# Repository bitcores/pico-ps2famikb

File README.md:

# pico-usb2famikb
Raspberry Pi Pico driven multi device emulator and Keyboard and Mouse Host for Famicom/NES by direct USB input or with an i2c host device

Emulates
* Family Basic Keyboard
* Subor Keyboard and Mouse
* Hori Track

And supports Keyboard and Mouse Host mode, a community developed serialized keyboard and mouse interface.

- \* D0 is only needed for subor mouse support. Connecting it will conflict with controller 2, it can be left disconnected. 4016 D1 shares this pin, it is only needed for Hori Track support on Famicom.
- \# D1 and D2 are only needed for Family Basic Keyboard mode, these can be left disconnected (esp. if making for NES player 2 controller port)
- \? USB D+ and D- lines are only needed for direct input. These can be left disconnected if only the i2c Host will be used (i2c Host EN can then be tied to 3.3V to permanently enable it)

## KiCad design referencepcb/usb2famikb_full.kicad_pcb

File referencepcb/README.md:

# pico-usb2famikb Reference PCBs
This directory contains reference PCB designs for the pico-usb2famikb. They have not been designed by a experienced engineer, but they DO work.

If you have some experience designing circuits like this, I would very much welcome improved designs.

For the full featured reference design you will need:
* 1x Raspberry Pi Pico
* 1x diode (I am using a 1N5819)
* 1x push button
* 1x 15pin d-sub VGA connector (for expansion port)
* 1x USB A type female port
* 2x 22ohm resistors
* 1x 100uf 16v capacitor (input from console)
* 1x 330uf 16v capacitor
* 2x four-channel logic level converters
* 13x pin headers (and some jumpers)

Note: The 330uf capactior was added because some USB3 hubs seem to draw significant power on startup can could crash the console or Pico, or both. The USB2 hubs I tested don't seem affected, but you can also just plug everything in before you turn on the console to avoid any issues.

## Wiring guide
The expansion port connector is laid out as follows when viewed from the top.

It is wired following the pinout of the [Famicom Expansion Port](https://www.nesdev.org/wiki/Expansion_port), 01 to 01, 15 to 15.
Wiring for the NES is more complicated, please reference both the tables on that page for wiring.

## Jumper guide
### KB Mode
The pico-usb2famikb can operate in four different modes:
 - Keyboard Mouse Host
 - Family Basic Keyboard
 - Subor Keyboard and Mouse
 - Family Basic Keyboard and HoriTrack

These modes are selected by setting the KBMode jumpers before power on (or reset).

 - No jumpers = Keyboard Mouse Host
 - One jumper on KBMode 1 = Family Basic Keyboard
 - One jumper on KBMode 2 = Subor Keyboard and Mouse
 - Two jumpers on KBMode 1 and 2 = Family Basic Keyboard and HoriTrack

### 4016D1/4017D0
HoriTrack and Subor Mouse require an extra data line which may interfere with controllers if left permanantly connected.

 - 4017d0 for Subor Mouse
 - 4016d1 for HoriTrack

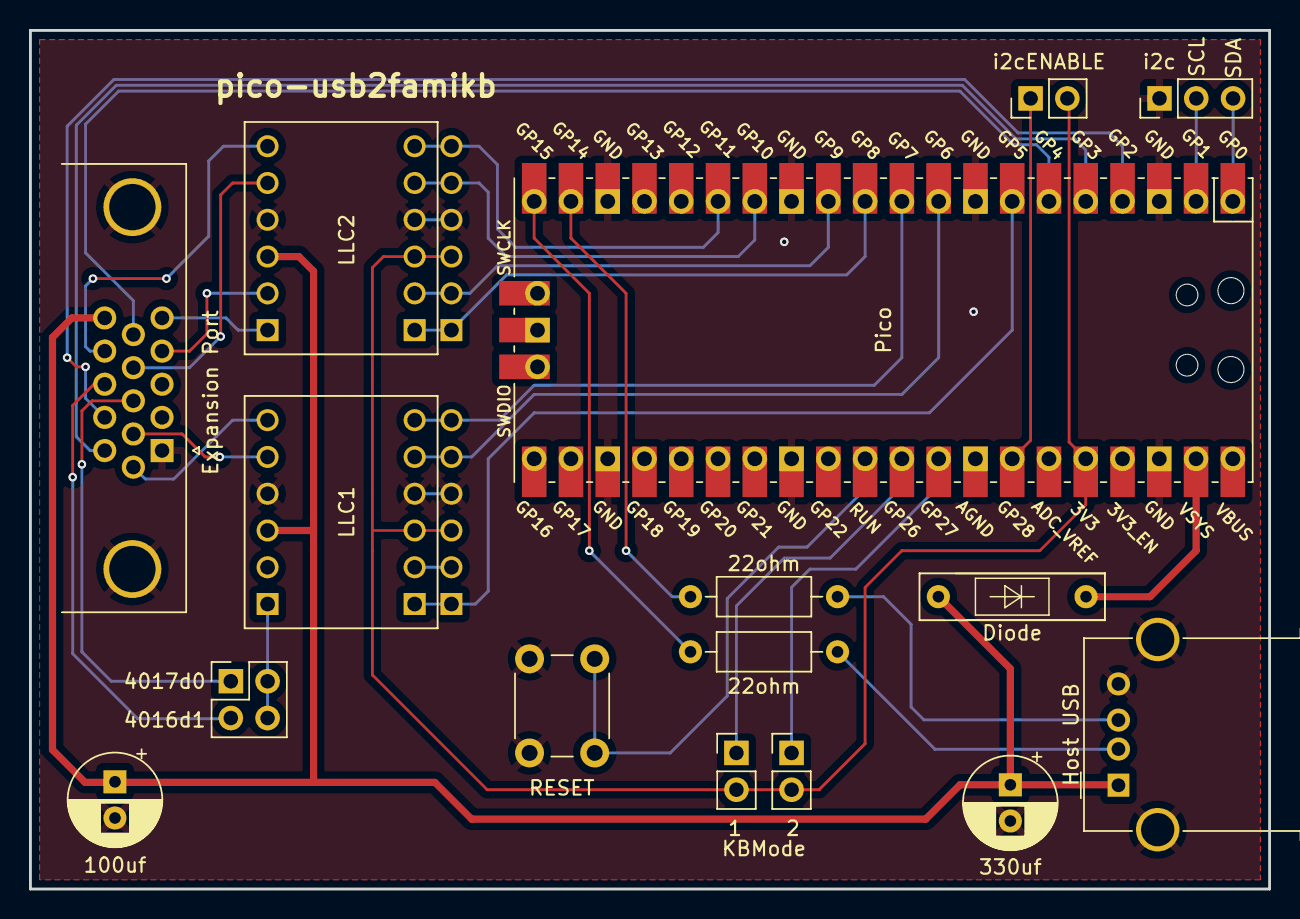
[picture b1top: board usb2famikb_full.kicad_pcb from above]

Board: 2 copper layers, 85.6 x 59.3 mm, 16 parts (0 on the bottom side), 33 nets.

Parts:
1    2: PinHeader_1x02_P2.54mm_Vertical
22ohm, 22ohm#2: R_Axial_DIN0207_L6.3mm_D2.5mm_P10.16mm_Horizontal
100uf, 330uf: CP_Radial_D6.3mm_P2.50mm
4017d0: PinHeader_2x02_P2.54mm_Vertical
Diode: D_MELF-RM10_Universal_Handsoldering
Expansion Port: DSUB-15-HD_Female_Horizontal_P2.29x1.98mm_EdgePin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; DSUB-15-HD_Female_Horizontal_P2.29x1.98mm_EdgePinOffset3.03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
Host USB: USB_A_Molex_67643_Horizontal
KBMode: PinHeader_1x02_P2.54mm_Vertical
LLC1, LLC2: CONV_BOB-12009
Pico: RPi_Pico_SMD_TH
RESET: SW_PUSH_6mm
i2c: PinHeader_1x03_P2.54mm_Vertical
i2cENABLE: PinHeader_1x02_P2.54mm_Vertical

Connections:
4016d1: 4017d0.3, Expansion Port.13
4016oe: Expansion Port.14, LLC2.HV4
4017d0: 4017d0.1, Expansion Port.8
4017d1: Expansion Port.7, LLC1.HV3
4017d2: Expansion Port.6, LLC1.HV4
4017d3: Expansion Port.5, LLC2.HV1
4017d4: Expansion Port.4, LLC2.HV2
4017oe: Expansion Port.9, LLC2.HV3
+3.3v: 1 2.2, KBMode.2, LLC1.LV, LLC2.LV, Pico.36, i2cENABLE.2
+5v: 100uf.1, 330uf.1, Diode.2, Expansion Port.15, Host USB.1, LLC1.HV, LLC2.HV
GND: 100uf.2, 330uf.2, Expansion Port.0, Expansion Port.1, Host USB.4, Host USB.5, LLC1.GND_1, LLC1.GND_2, LLC2.GND_1, LLC2.GND_2, Pico.3, Pico.8, Pico.13, Pico.18, Pico.23, Pico.28, Pico.33, Pico.38, RESET.2, i2c.1
fcd0d1: 4017d0.2, 4017d0.4, LLC1.HV1
fcout0: Expansion Port.12, Pico.4
fcout1: Expansion Port.11, Pico.5
fcout2: Expansion Port.10, Pico.6
i2c1: Pico.1, i2c.3
i2c2: Pico.2, i2c.2
i2chosten: Pico.34, i2cENABLE.1
kbmode0: KBMode.1, Pico.31
kbmode1: 1 2.1, Pico.32
pico5v: Diode.1, Pico.39
pico4016oe: LLC2.LV4, Pico.15
pico4017d1: LLC1.LV3, Pico.9
pico4017d2: LLC1.LV4, Pico.10
pico4017d3: LLC2.LV1, Pico.11
pico4017d4: LLC2.LV2, Pico.12
pico4017oe: LLC2.LV3, Pico.14
pico_usb_d+: 22ohm.2, Pico.19
pico_usb_d-: 22ohm#2.2, Pico.20
picod0d1: LLC1.LV1, Pico.7
resetbtn: Pico.30, RESET.1
usb_d+: 22ohm.1, Host USB.3
usb_d-: 22ohm#2.1, Host USB.2

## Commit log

2024-04-03 initial release
2024-04-03 sample build file from current code
2024-04-06 rearrange ps2kbd license and readme
2024-04-13 support D0
    changes that allow D0 to be connected for future modes
2024-04-23 add test rom
    test rom for family basic keyboard
2024-04-29 second test rom
    test rom for the ps/2 input mode, displays controller 2, keyboard and mouse
2024-04-29 second mode support added
    added support for serialized ps/2 mode
2024-05-10 preparation for kb layout select
    beginning of being able to select from multiple keyboard layouts
2024-05-11 begin subor kb support
    add the map and modify keymatrix to support subor kb
2024-05-11 add schematic
    a semi reference schematic, work on progress
2024-05-25 revert layout select
    chosen layout will be decided when compiled for direct input (ps/2) mode. USB host mode will use do scancode conversion on the USB host
2024-06-05 prepare for i2c
    rearrangement of pins with preparation for i2c usb host support
2024-06-09 usbhost support
    usbhost support added via i2c
2024-06-09 add usbhost software
    the usbhost software and some readmes
2024-06-16 usbhost full implement
    The USBHost mode is now fully implemented with support for remapping on the host side, relative mode for mouse cursor movement, mouse wheel and middle button.
    It may be possible to lose some events on the mouse wheel and/or middle button, this could be fixed later.
    Also included wiring guides for Pico and Pico-Zero.
2024-06-16 Update README.md
    add images and update readme
2024-06-23 prevent buffer overrun
    prevent buffer overrunning and simple out of spec i2c message detection.
    Too much work is likely being done in the i2c message handler which can result in a visible backlog of key press events, or at least that is what I assume is happening
2024-06-30 introduce keyboard double buffer
    use a double buffer to prevent possible conflict in keybuffer. should add 0 - 1 frame of latency
2024-07-11 preparations for subor mode
    changed the way mode is read and the applied
2024-07-17 Hold repeats option
    When enabled holding a key down will send the "down" code repeatedly until key is released or another key is pressed.
    This is normal behavior on ps/2 and USB keyboards, it should be up to the NES program to handle repeats but it is configurable here as well.
2024-07-24 added subor keyboard support
    Begin support for subor keyboard, mouse to come
2024-08-16 subor updates
    Added message to usbhost software config to only use relative mouse mode when using subor or HoriTrack.
    Fixed subor key layout (was mirrored).
    Always update mouse data if mouse present on usbhost, not just keyboard/mouse host mode.
    More prep for subor mouse support.
2024-08-24 main subor implementation
    Lots of big changes.
    Changed to using PIO IRQs to reduce CPU time and speed up updates from console.
    Changed keyboard/mouse data to be non-inverted until it is output.
    Fixed relative mouse in usbhost.
    Subor keyboard and mouse support implemented.
2024-08-25 Initial Hori Track support
    Basic Hori Track support implemented
    Updated wiring guides
2024-08-27 Hori Track options
    introduce Hori Track switch options
    new full feature test build
2024-08-31 guide updates, some code changes
2024-08-31 fixed tabs
2024-09-16 rel mouse overflow fix
    Fix the mouse x/y overflowing in relative mode
    Little bit of cleanup in pio
2024-09-24 remove ps/2
    remove the libraries for ps/2 in preparation for pio-usb
2024-09-24 import pico-pio-usb
2024-09-27 PIO/SM configuration
    set up configuration assignments for the PIOs and SMs
2024-09-28 initial usb implementation
2024-09-29 rename usbhost -> i2chost
    With onboard usb, usbhost is now poorly named. Rename it more descriptively
2024-09-29 remove ps2 naming, go to usb
2024-09-29 finish build rename
2024-09-30 fix famikey+hori
    force the SM to output the data onto the pins as well, rather than including that in the loop, because otherwise we need to wait on both output enables and we don't have the spare SMs for that
2024-10-04 refactoring
    remove unused variables
    rename to usb2famikb
    condense input handling
2024-10-04 refactor and fix keycode releases
    function renames
    fix how keyboard key releases is detected and some minor mouse update
2024-10-04 update readme and guides
2024-10-22 reference pcb added
2024-10-30 fix mistake in readme
2024-11-30 clearly name gerber zip file
2024-12-14 build with led disabled for pico-w type boards
2024-12-14 perhaps correctly built uf2 for picow?
2024-12-19 updated test apps
2024-12-30 referencepcb docs and license updates
    more information for reference PCB wiring and config
    consolidate software licenses
2025-01-07 1.0.1 updates
    support for pico-w (experimental)
    reduced pico overclock
    keyboard modifier key handling (ctrl, shift, alt, meta)
2025-01-16 #4 Improve NES state handling
    State of NES outputs cannot be trusted when interface starts or resets.
    Interface will now enter output monitoring properly regardless of high or low states.
2025-01-18 #4 Fix Family Basic Keyboard
    Fixed output when disabled (no longer interfere with controller input)
    Rearranged Family Basic Keyboard mapping to better fit US keyboard layout
    Removed old testapps and unnecessary pullups
